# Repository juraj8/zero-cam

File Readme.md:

# Zero Cam

Zero Cam is open security camera based on Raspberry Pi Zero. This solution should be an alternative to low cost IP cameras.
One advantage is upgradeability of software running the camera is that it always can be updated to add support to various technologies, which cannot be achieved with other cheap cameras.

## Features 

* Ethernet 100/10 BaseT with passive POE
* IR light for night vision,
* Temperature and humanity sensor,
* Can be powered by external DC powerfully 24~48V
* Can use any Raspberry Pi compatible camera module.

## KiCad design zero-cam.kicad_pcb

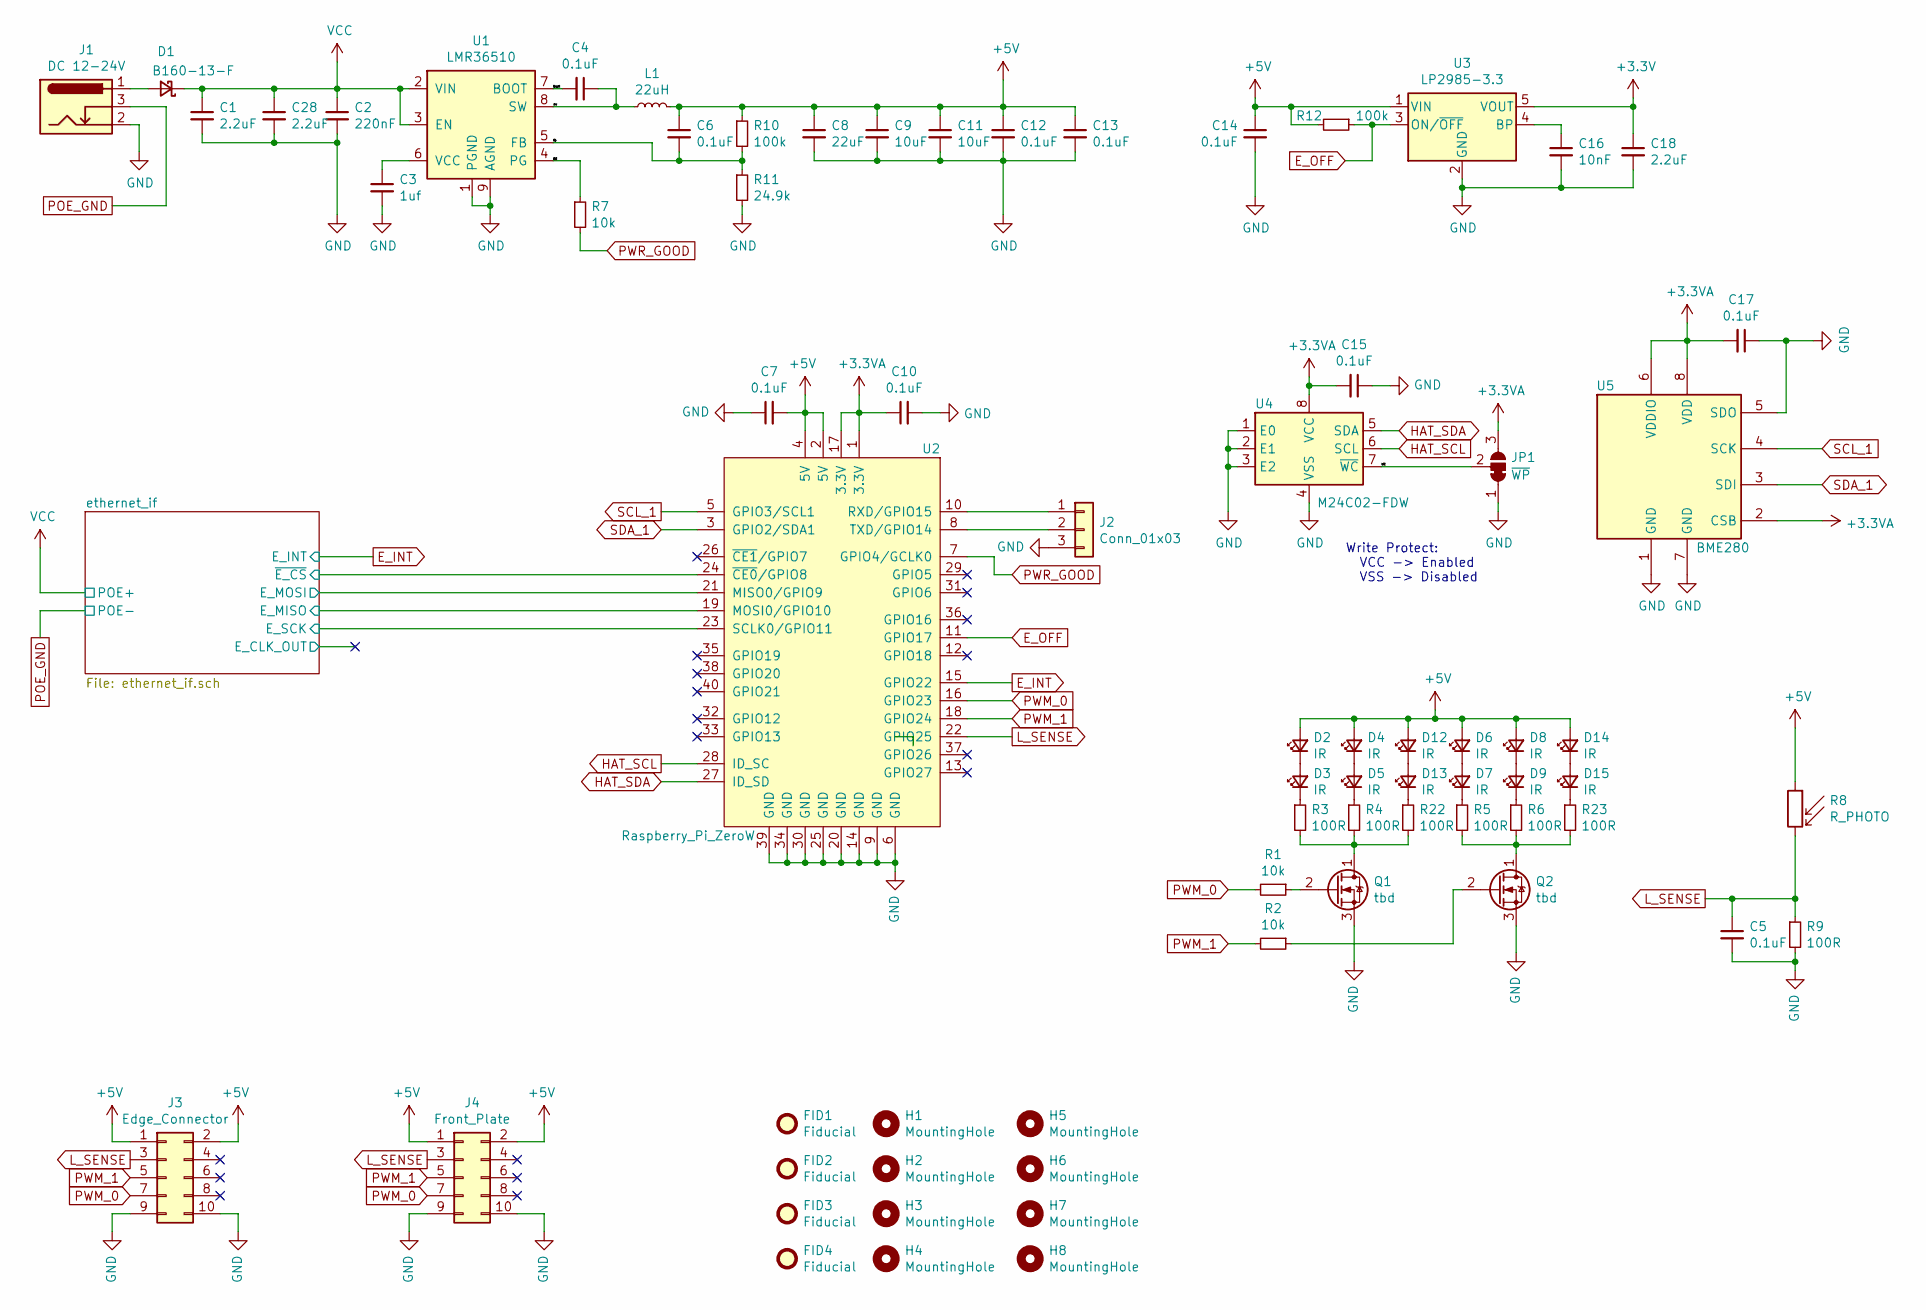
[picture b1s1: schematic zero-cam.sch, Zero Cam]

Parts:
C1, C28: 2.2uF; C_1210_3225Metric_Pad1.33x2.70mm_HandSolder
C2: 220nF; C_0805_2012Metric_Pad1.18x1.45mm_HandSolder
C3: 1uf; C_0805_2012Metric_Pad1.18x1.45mm_HandSolder
C4, C5, C6, C7, C10, C12, C14, C15, C17: 0.1uF; C_0805_2012Metric_Pad1.18x1.45mm_HandSolder
C8: 22uF; C_1206_3216Metric_Pad1.33x1.80mm_HandSolder
C9, C11: 10uF; C_1206_3216Metric_Pad1.33x1.80mm_HandSolder
C13: 0.1uF; C_0603_1608Metric_Pad1.08x0.95mm_HandSolder
C16: 10nF; C_0805_2012Metric_Pad1.18x1.45mm_HandSolder
C18: 2.2uF; C_0805_2012Metric_Pad1.18x1.45mm_HandSolder
D1: B160-13-F; D_SMA_Handsoldering
D2, D3, D4, D5, D6, D7, D8, D9, D12, D13, D14, D15: IR; LED_0805_2012Metric_Pad1.15x1.40mm_HandSolder
FID1, FID2, FID3, FID4: Fiducial; Fiducial_0.5mm_Mask1mm
H1, H2, H3, H4, H5, H6, H7, H8: MountingHole; MountingHole_3.2mm_M3_DIN965
J1: DC 12-24V; BarrelJack_Horizontal
J2: Conn_01x03; PinHeader_1x03_P2.54mm_Vertical
J3: Edge_Connector; Edge_PinHeader_2x05_P2
J4: Front_Plate; PinSocket_2x05_P2.54mm_Vertical
JP1: ~WP~; SolderJumper-3_P1.3mm_Bridged12_RoundedPad1.0x1.5mm_NumberL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
L1: 22uH; L_10.4x10.4_H4.8
Q1, Q2: tbd; TSOT-23
R1, R2, R7: 10k; R_0805_2012Metric_Pad1.20x1.40mm_HandSolder
R3, R4, R5, R6, R9, R22, R23: 100R; R_0805_2012Metric_Pad1.20x1.40mm_HandSolder
R8: R_PHOTO; R_LDR_4.9x4.2mm_P2.54mm_Vertical
R10, R12: 100k; R_0805_2012Metric_Pad1.20x1.40mm_HandSolder
R11: 24.9k; R_0805_2012Metric_Pad1.20x1.40mm_HandSolder
U1: LMR36510; Texas_HSOP-8-1EP_3.9x4.9mm_P1.27mm_ThermalVias
U2: Raspberry_Pi_ZeroW; Raspberry_Pi_Zero_Socketed_THT_FaceDown_MountingHoles
U3: LP2985-3.3; SOT-23-5
U4: M24C02-FDW; TSSOP-8_4.4x3mm_P0.65mm
U5: BME280; Bosch_LGA-8_2.5x2.5mm_P0.65mm_ClockwisePinNumbering

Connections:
+3.3VA: C10.1, C15.2, C17.2, JP1.3 (B), U2.1 (3.3V), U2.17 (3.3V), U4.8 (VCC), U5.2 (CSB), U5.6 (VDDIO), U5.8 (VDD)
+3V3: C18.1, U3.5 (VOUT); also elsewhere on the board
+5V: C6.1, C7.2, C8.1, C9.1, C11.1, C12.1, C13.1, C14.1, D2.2 (A), D4.2 (A), D6.2 (A), D8.2 (A), D12.2 (A), D14.2 (A), J3.1, J3.2, J4.1, J4.2, L1.2, R8.1, R10.1, R12.2, U2.2 (5V), U2.4 (5V), U3.1 (VIN)
/WC: JP1.2 (C), U4.7 (~WC)
/boot: C4.2, U1.7 (BOOT)
/ethernet_if/E_MISO: U2.19 (MOSI0/GPIO10); also elsewhere on the board
/ethernet_if/E_MOSI: U2.21 (MISO0/GPIO9); also elsewhere on the board
/ethernet_if/E_SCK: U2.23 (SCLK0/GPIO11); also elsewhere on the board
/ethernet_if/~E_CS~: U2.24 (~CE0~/GPIO8); also elsewhere on the board
/fb: C6.2, R10.2, R11.1, U1.5 (FB)
/pg: R7.1, U1.4 (PG)
/sw: C4.1, L1.1, U1.8 (SW)
E_INT: U2.15 (GPIO22); also elsewhere on the board
E_OFF: R12.1, U2.11 (GPIO17), U3.3 (ON/~OFF~)
GND: C1.2, C2.2, C3.2, C5.2, C7.1, C8.2, C9.2, C10.2, C11.2, C12.2, C13.2, C14.2, C15.1, C16.2, C17.1, C18.2, C28.2, J1.2, J2.3, J3.9, J3.10, J4.9, J4.10, JP1.1 (A), Q1.3 (S), Q2.3 (S), R9.2, R11.2, U1.1 (PGND), U1.9 (AGND), U2.6 (GND), U2.9 (GND), U2.14 (GND), U2.20 (GND), U2.25 (GND), U2.30 (GND), U2.34 (GND), U2.39 (GND), U3.2 (GND), U4.1 (E0), U4.2 (E1), U4.3 (E2), U4.4 (VSS), U5.1 (GND), U5.5 (SDO), U5.7 (GND); also elsewhere on the board
HAT_SCL: U2.28 (ID_SC), U4.6 (SCL)
HAT_SDA: U2.27 (ID_SD), U4.5 (SDA)
L_SENSE: C5.1, J3.3, J4.3, R8.2, R9.1, U2.22 (GPIO25)
unnamed: C3.1, U1.6 (VCC)
unnamed: C16.1, U3.4 (BP)
unnamed: D1.2 (A), J1.1
unnamed: D2.1 (K), D3.2 (A)
unnamed: D3.1 (K), R3.1
unnamed: D4.1 (K), D5.2 (A)
unnamed: D5.1 (K), R4.1
unnamed: D6.1 (K), D7.2 (A)
unnamed: D7.1 (K), R5.1
unnamed: D8.1 (K), D9.2 (A)
unnamed: D9.1 (K), R6.1
unnamed: D12.1 (K), D13.2 (A)
unnamed: D13.1 (K), R22.1
unnamed: D14.1 (K), D15.2 (A)
unnamed: D15.1 (K), R23.1
unnamed: J2.1, U2.10 (RXD/GPIO15)
unnamed: J2.2, U2.8 (TXD/GPIO14)
unnamed: Q1.1 (D), R3.2, R4.2, R22.2
unnamed: Q1.2 (G), R1.1
unnamed: Q2.1 (D), R5.2, R6.2, R23.2
unnamed: Q2.2 (G), R2.1
POE+: C1.1, C2.1, C28.1, D1.1 (K), U1.2 (VIN), U1.3 (EN); also elsewhere on the board
POE-: J1.3; also elsewhere on the board
PWM_0: J3.7, J4.7, R1.2, U2.16 (GPIO23)
PWM_1: J3.5, J4.5, R2.2, U2.18 (GPIO24)
PWR_GOOD: R7.2, U2.7 (GPIO4/GCLK0)
SCL_1: U2.5 (GPIO3/SCL1), U5.4 (SCK)
SDA_1: U2.3 (GPIO2/SDA1), U5.3 (SDI)

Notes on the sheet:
Write Protect: VCC -> Enabled VSS -> Disabled

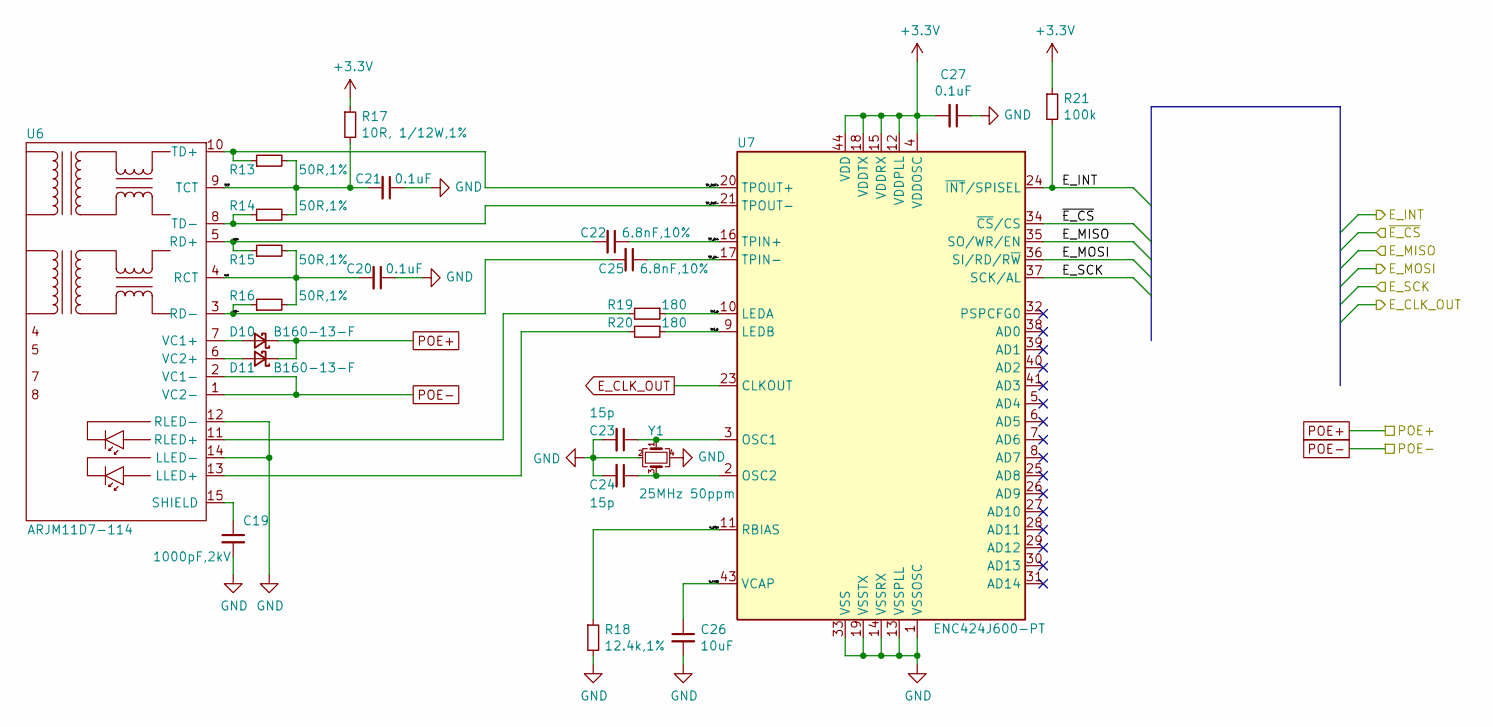
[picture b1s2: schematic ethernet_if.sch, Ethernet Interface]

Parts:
C19: 1000pF,2kV; C_0805_2012Metric_Pad1.18x1.45mm_HandSolder
C20, C21, C27: 0.1uF; C_0805_2012Metric_Pad1.18x1.45mm_HandSolder
C22, C25: 6.8nF,10%; C_0805_2012Metric_Pad1.18x1.45mm_HandSolder
C23, C24: 15p; C_0805_2012Metric_Pad1.18x1.45mm_HandSolder
C26: 10uF; C_0805_2012Metric_Pad1.18x1.45mm_HandSolder
D10, D11: B160-13-F; D_SMA_Handsoldering
R13, R14, R15, R16: 50R,1%; R_0805_2012Metric_Pad1.20x1.40mm_HandSolder
R17: 10R, 1/12W,1%; R_0805_2012Metric_Pad1.20x1.40mm_HandSolder
R18: 12.4k,1%; R_0805_2012Metric_Pad1.20x1.40mm_HandSolder
R19, R20: 180; R_0805_2012Metric_Pad1.20x1.40mm_HandSolder
R21: 100k; R_0805_2012Metric_Pad1.20x1.40mm_HandSolder
U6: ARJM11D7-114
U7: ENC424J600-PT; TQFP-44_10x10mm_P0.8mm
Y1: 25MHz 50ppm; Crystal_SMD_3225-4Pin_3.2x2.5mm_HandSoldering

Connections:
+3V3: C27.2, R17.1, R21.1, U7.4 (VDDOSC), U7.12 (VDDPLL), U7.15 (VDDRX), U7.18 (VDDTX), U7.44 (VDD); also elsewhere on the board
/ethernet_if/E_MISO: U7.35 (SO/WR/EN); also elsewhere on the board
/ethernet_if/E_MOSI: U7.36 (SI/RD/R~W); also elsewhere on the board
/ethernet_if/E_SCK: U7.37 (SCK/AL); also elsewhere on the board
/ethernet_if/TCT: C21.2, R13.2, R14.2, R17.2, U6.9 (TCT)
/ethernet_if/TP_IN+: C22.1, U7.16 (TPIN+)
/ethernet_if/TP_IN-: C25.1, U7.17 (TPIN-)
/ethernet_if/TP_OUT+: R13.1, U6.10 (TD+), U7.20 (TPOUT+)
/ethernet_if/TP_OUT-: R14.1, U6.8 (TD-), U7.21 (TPOUT-)
/ethernet_if/e_bias: R18.1, U7.11 (RBIAS)
/ethernet_if/e_vcap: C26.1, U7.43 (VCAP)
/ethernet_if/led_a: R19.1, U7.10 (LEDA)
/ethernet_if/led_b: R20.1, U7.9 (LEDB)
/ethernet_if/rct: C20.2, R15.2, R16.2, U6.4 (RCT)
/ethernet_if/rd+: C22.2, R15.1, U6.5 (RD+)
/ethernet_if/rd-: C25.2, R16.1, U6.3 (RD-)
/ethernet_if/~E_CS~: U7.34 (~CS~/CS); also elsewhere on the board
E_CLK_OUT: U7.23 (CLKOUT)
E_INT: R21.2, U7.24 (~INT~/SPISEL); also elsewhere on the board
GND: C19.2, C20.1, C21.1, C23.2, C24.2, C26.2, C27.1, R18.2, U6.12 (RLED-), U6.14 (LLED-), U7.1 (VSSOSC), U7.13 (VSSPLL), U7.14 (VSSRX), U7.19 (VSSTX), U7.22 (VSSTX), U7.33 (VSS), U7.42 (VSS), Y1.2, Y1.4; also elsewhere on the board
unnamed: C19.1, U6.15 (SHIELD)
unnamed: C23.1, U7.3 (OSC1), Y1.1
unnamed: C24.1, U7.2 (OSC2), Y1.3
unnamed: D10.2 (A), U6.7 (VC1+)
unnamed: D11.2 (A), U6.6 (VC2+)
unnamed: R19.2, U6.11 (RLED+)
unnamed: R20.2, U6.13 (LLED+)
POE+: D10.1 (K), D11.1 (K); also elsewhere on the board
POE-: U6.1 (VC2-), U6.2 (VC1-); also elsewhere on the board

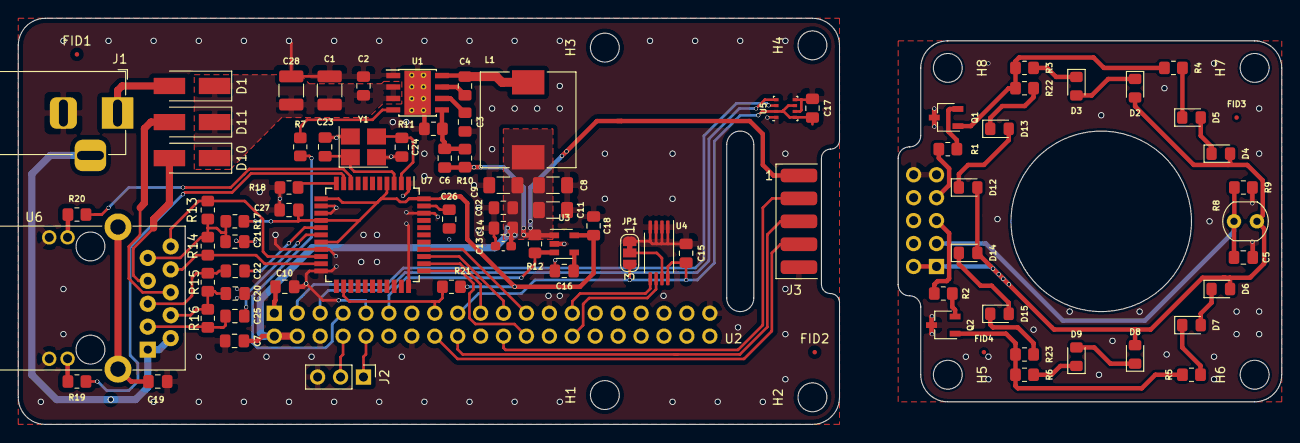
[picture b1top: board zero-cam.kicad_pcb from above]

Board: 2 copper layers, 140.0 x 45.0 mm, 94 parts (1 on the bottom side), 65 nets.

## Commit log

2021-04-24 Added rpi library, readme
2021-04-25 Added project common library.
2021-04-25 Schematic rc1 finished.
2021-04-25 Added pcb file.
2021-04-27 Change for actual footprints, raff board done.
2021-04-29 Connector placment done, dimentions decided ...
2021-04-30 start layout
2021-05-01 Layout almost done
2021-05-02 Set theme jekyll-theme-minimal
2021-05-02 Release v0.2.0
